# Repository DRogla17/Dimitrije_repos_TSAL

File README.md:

# Dimitrije_repos_TSAL
Repository made for TSAL part of Formula Student vehicle for Black Hornets Formula Student Team from Faculty of Technical Sciences, Novi Sad.

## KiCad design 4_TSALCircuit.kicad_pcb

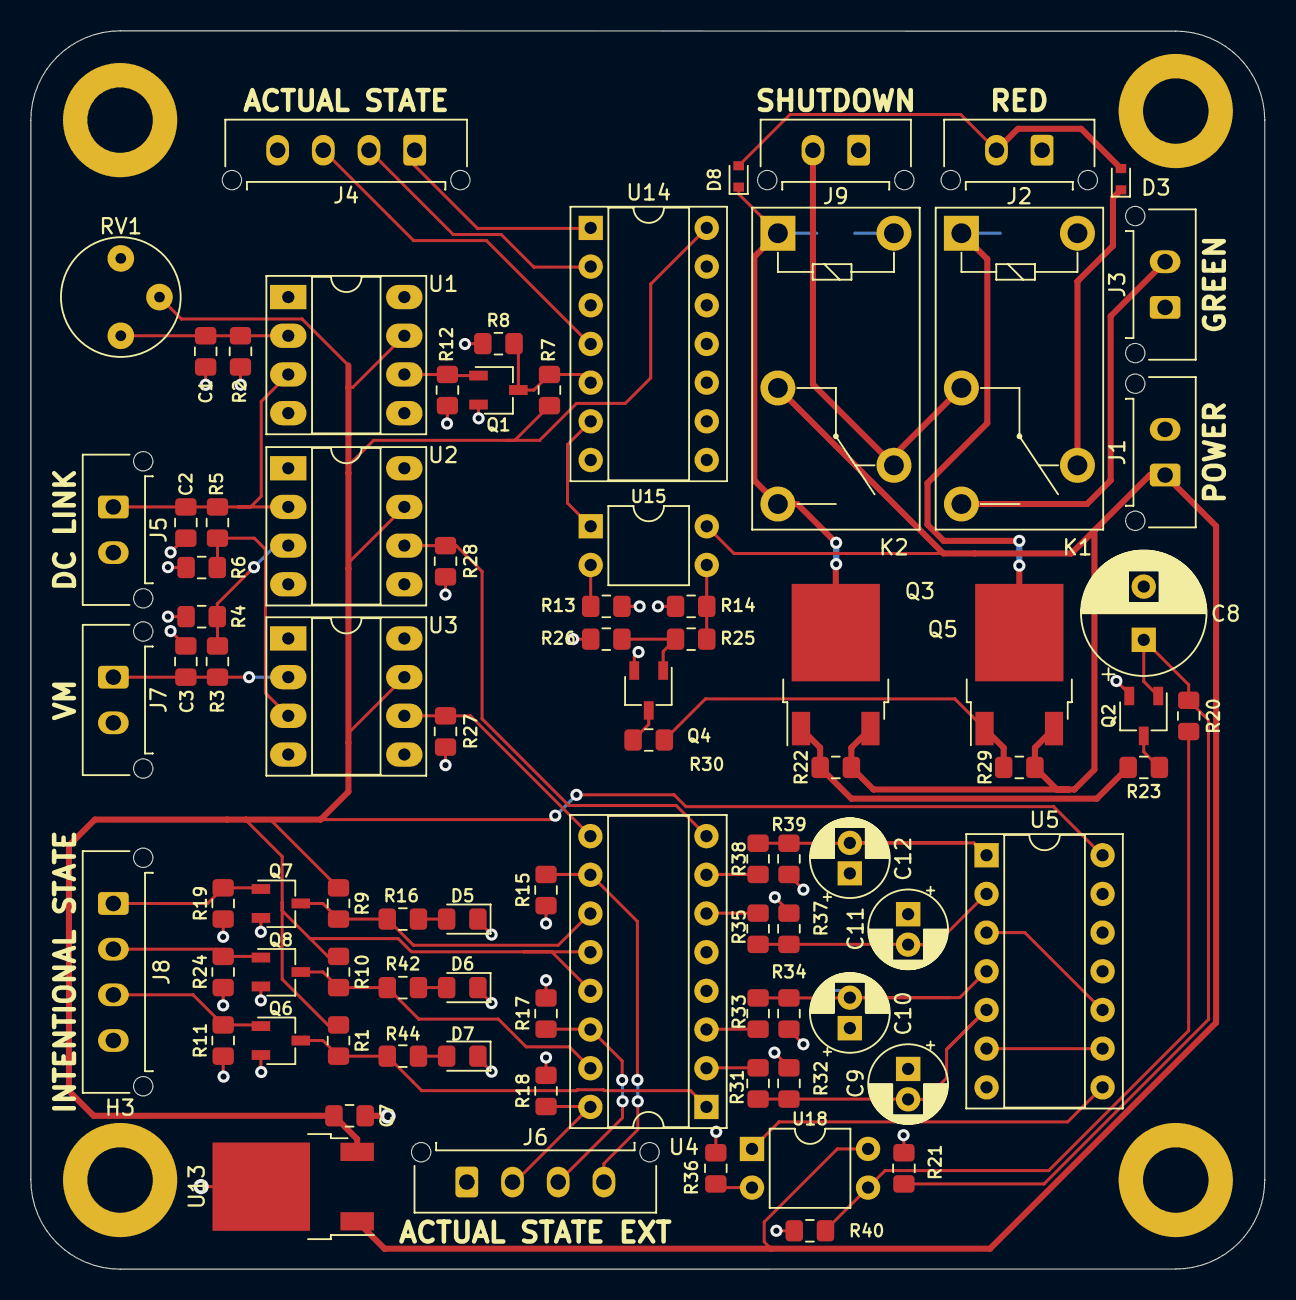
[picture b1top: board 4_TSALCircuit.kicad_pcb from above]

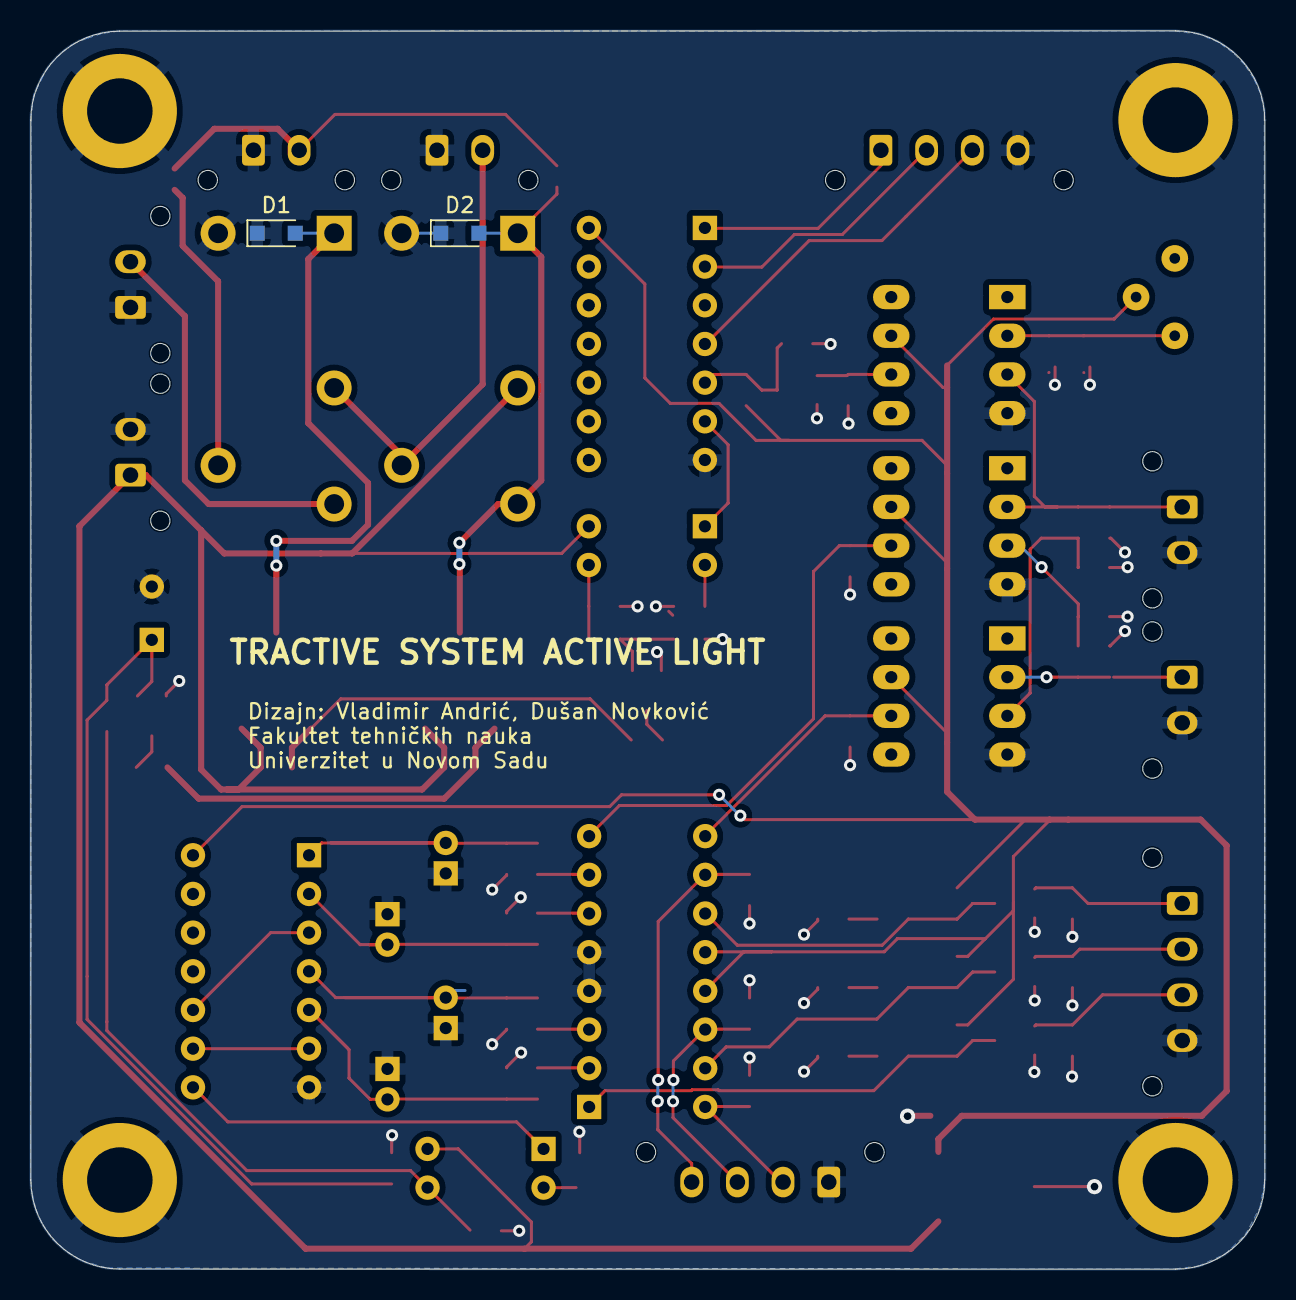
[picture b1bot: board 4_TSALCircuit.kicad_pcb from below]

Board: 2 copper layers, 81.0 x 81.3 mm, 91 parts (2 on the bottom side), 55 nets.

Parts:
C1, C2, C3: 10nF; C_0805_2012Metric_Pad1.15x1.40mm_HandSolder
C7: 100n; C_0805_2012Metric_Pad1.15x1.40mm_HandSolder
C8: 340u; CP_Radial_D8.0mm_P3.50mm
C9, C10, C11, C12: 10u; CP_Radial_D5.0mm_P2.00mm
D1, D2: DIODE; D_SOD-323_HandSoldering
D3, D8: DIODE; D_SOD-523
D5, D6, D7: LED; LED_0805_2012Metric_Pad1.15x1.40mm_HandSolder
H1, H2, H3, H4: MountingHole_Pad; MountingHole_4.3mm_M4_DIN965_Pad
J1: Power; Molex_Micro-Fit_3.0_43650-0215_1x02_P3.00mm_Vertical
J2: Red Light; Molex_Micro-Fit_3.0_43650-0215_1x02_P3.00mm_Vertical
J3: Green Light; Molex_Micro-Fit_3.0_43650-0215_1x02_P3.00mm_Vertical
J4, J6: Actual State; Molex_Micro-Fit_3.0_43650-0415_1x04_P3.00mm_Vertical
J5: VM DC Link Capacitor; Molex_Micro-Fit_3.0_43650-0215_1x02_P3.00mm_Vertical
J7: VM TSAC; Molex_Micro-Fit_3.0_43650-0215_1x02_P3.00mm_Vertical
J8: Intentional State; Molex_Micro-Fit_3.0_43650-0415_1x04_P3.00mm_Vertical
J9: Error_to_SHD; Molex_Micro-Fit_3.0_43650-0215_1x02_P3.00mm_Vertical
K1, K2: G5Q-1; Relay_SPDT_Omron-G5Q-1
Q1, Q2, Q4, Q6, Q7, Q8: Q_NMOS_GDS; TSOT-23
Q3, Q5: PMOS; TO-252-2
R1, R3, R5, R8, R9, R10, R11, R14, R15, R17, R18, R19, R22, R24, R27, R28, R29, R40: 10k; R_0805_2012Metric_Pad1.15x1.40mm_HandSolder
R2, R20: 5k; R_0805_2012Metric_Pad1.15x1.40mm_HandSolder
R4, R6: 47k; R_0805_2012Metric_Pad1.15x1.40mm_HandSolder
R7, R12, R13, R16, R23, R30, R31, R33, R35, R36, R38, R42, R44: 1k; R_0805_2012Metric_Pad1.15x1.40mm_HandSolder
R21, R26, R32, R34, R37, R39: 100k; R_0805_2012Metric_Pad1.15x1.40mm_HandSolder
R25: 34k; R_0805_2012Metric_Pad1.15x1.40mm_HandSolder
RV1: R_POT; Potentiometer_Bourns_3339P_Vertical_HandSoldering
U1, U2, U3: MCP6541; DIP-8_W7.62mm_Socket_LongPads
U4: 74AC11086; DIP-16_W7.62mm_Socket
U5: SN74LVC32AD; DIP-14_W7.62mm_Socket
U13: NCV7805BDTRKG; TO-252-2
U14: SN74HC21NX; DIP-14_W7.62mm_Socket
U15, U18: SFH617A-1; DIP-4_W7.62mm

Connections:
+5V: C7.1, R1.1, R7.1, R9.1, R10.1, RV1.2, U1.7, U2.7, U3.7, U4.12, U4.13, U5.14, U13.3, U14.14
+12V: J1.1, K2.2, Q3.3, Q5.3, R22.1, R29.1, U13.1, U15.4, U18.4
/Act_State_1: J4.1, U14.1
/Act_State_2: J4.2, U14.2
/Act_State_3: J4.3, U14.4
/Act_State_Ext_1: J6.4, R15.1, U4.10
/Act_State_Ext_2: J6.3, R17.1, U4.14
/Act_State_Ext_3: J6.2, R18.1, U4.16
/Error_Shutdown: J9.2, K1.2, K2.4
/GreenLight_ON: R14.1, R25.1, U15.3
/Green_Light: J3.2, K1.3
/Int_Out_1: Q7.3, R9.2, R16.1, U4.11
/Int_Out_2: Q8.3, R10.2, R42.1, U4.15
/Int_Out_3: Q6.3, R1.2, R44.1, U4.1
/Int_State_1: J8.1, Q7.1, R19.1
/Int_State_2: J8.2, Q8.1, R24.1
/Int_State_3: J8.3, Q6.1, R11.1
/RedLight_LATCHED: R20.1, R40.1, U18.3
/Red_Light: D3.2, D8.2, J2.2
/VM_DC_Link: C2.1, J5.1, R5.1, U1.3, U2.2
/VM_TSAC: C3.1, J7.1, R3.1, U3.2
GND: C1.2, C2.2, C3.2, C7.2, C8.2, C9.1, C10.1, C11.1, C12.1, D1.1, D2.1, D5.1, D6.1, D7.1, H1.1, H2.1, H3.1, H4.1, J1.2, J2.1, J3.1, J4.4, J5.2, J6.1, J7.2, J8.4, J9.1, K1.5, K2.5, Q1.2, Q2.2, Q4.2, Q6.2, Q7.2, Q8.2, R2.2, R4.2, R6.2, R8.2, R11.2, R12.2, R13.2, R14.2, R15.2, R17.2, R18.2, R19.2, R21.1, R24.2, R26.1, R27.2, R28.2, R32.2, R34.2, R36.2, R37.2, R39.2, R40.2, U1.4, U2.4, U3.4, U4.4, U4.5, U5.7, U13.2, U14.7
unnamed: C1.1, R2.1, RV1.3, U1.2
unnamed: C8.1, Q2.1, R20.2, R21.2
unnamed: C9.2, R31.1, R32.1, U5.5
unnamed: C10.2, R33.1, R34.1, U5.4
unnamed: C11.2, R35.1, R37.1, U5.2
unnamed: C12.2, R38.1, R39.1, U5.1
unnamed: D1.2, K1.1, Q5.2
unnamed: D2.2, D8.1, K2.1, K2.3, Q3.2
unnamed: D3.1, K1.4
unnamed: D5.2, R16.2
unnamed: D6.2, R42.2
unnamed: D7.2, R44.2
unnamed: Q1.1, R12.1, U1.6
unnamed: Q1.3, R7.2, R8.1, U14.5
unnamed: Q2.3, R23.2
unnamed: Q3.1, R22.2, R23.1
unnamed: Q4.1, R25.2, R26.2
unnamed: Q4.3, R30.2
unnamed: Q5.1, R29.2, R30.1
unnamed: R3.2, R4.1, U2.3
unnamed: R5.2, R6.1, U3.3
unnamed: R13.1, U15.2
unnamed: R27.1, U3.6, U4.9
unnamed: R28.1, U2.6, U4.8
unnamed: R31.2, U4.2
unnamed: R33.2, U4.3
unnamed: R35.2, U4.6
unnamed: R36.1, U18.2
unnamed: R38.2, U4.7
unnamed: U5.6, U5.9
unnamed: U5.3, U5.10
unnamed: U14.6, U15.1
unnamed: U5.8, U18.1

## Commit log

2026-04-28 Added KiCad model of PCB
